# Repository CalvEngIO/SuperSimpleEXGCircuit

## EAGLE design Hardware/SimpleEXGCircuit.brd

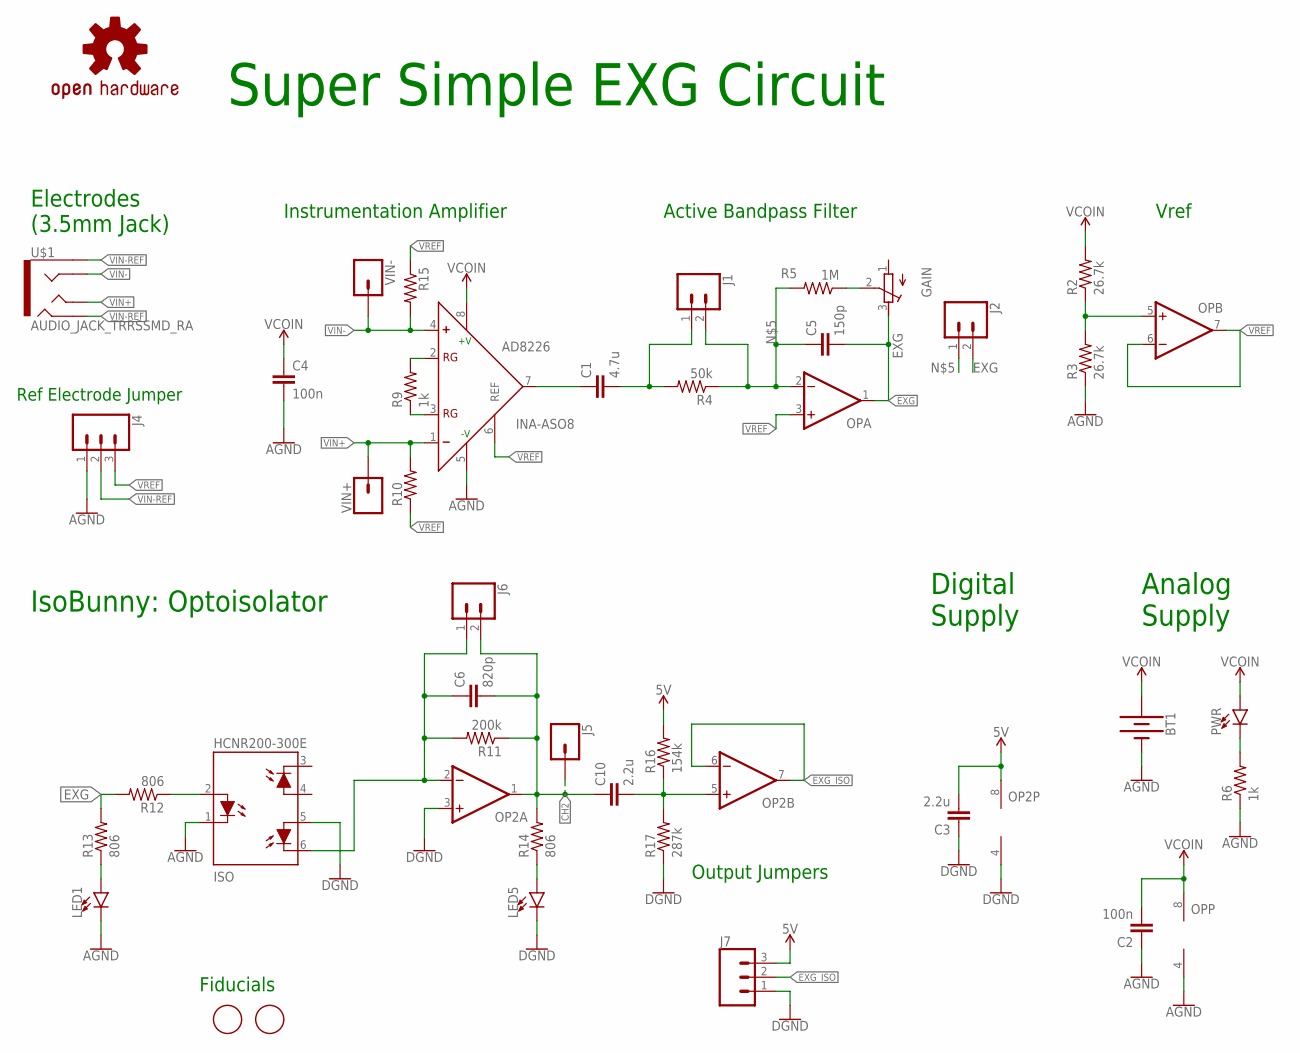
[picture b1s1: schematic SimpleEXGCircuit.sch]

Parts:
AD8226: INA-ASO8; SO8
BT1: BATTERY-20MM_SMD_4LEGS_OVERPASTE; BATTCON_20MM_4LEGS_OVERPASTE
C1: 4.7u; C0603
C2, C4: 100n; C0603
C3, C10: 2.2u; C0603
C5: 150p; C0603
C6: 820p; C0603
GAIN: TRIM-POT-P160; 16MMROTARYPOT
ISO: HCNR200-300E; DIP8-400
J1, J2, J6: CONN_02; 1X02
J4, J7: CONN_03; 1X03
J5: CONN_01PTH_NO_SILK_KIT; 1X01NS_KIT
LED1, LED5: LED1206; LED-1206
LOGO1: REVISION.C; REV.C
LOGO4: OSHW-LOGOL; OSHW-LOGO-L
OP, OP2: OP-DUALR; SO8
PWR: LED1206; LED-1206
R2, R3: 26.7k; R0603
R4: 50k; R0603
R5: 1M; R0603
R6, R9: 1k; R0603
R10, R15: RESISTOR0603; R0603
R11: 200k; R0603
R12, R13, R14: 806; R0603
R16: 154k; R0603
R17: 287k; R0603
U$1: AUDIO_JACK_TRRSSMD_RA; AUDIO_JACK_3.5MM_TRRS_SMD_RA
U$4: CALVENGIO_HANDLEHANDLE.05; CALVENGIO_HANDLE.05
U$5, U$6: FIDUCIAL; FIDUCIAL_1MM
VIN+: CONN_01; 1X01
VIN-: CONN_01; 1X01

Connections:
5V: C3.2, J7.3, OP2.8 (V+), R16.2
AGND: AD8226.5 (-V), BT1.2 (-), C2.1, C4.2, ISO.1 (C), J4.1, LED1.C, OP.4 (V-), R3.1, R6.1
CH2: C6.2, C10.1, J5.1, J6.2, OP2.1 (OUT), R11.1, R14.2
DGND: C3.1, ISO.5 (A2), J7.1, LED5.C, OP2.3 (+IN), OP2.4 (V-), R17.1
EXG: C5.2, GAIN.3 (E), J2.2, OP.1 (OUT), R12.2, R13.2
EXG_ISO: J7.2, OP2.6 (-IN), OP2.7 (OUT)
INA: AD8226.7 (OUT), C1.1
unnamed: GAIN.2 (S), R5.1
unnamed: AD8226.2 (RG), R9.2
unnamed: OP.5 (+IN), R2.1, R3.2
unnamed: C5.1, J1.2, J2.1, OP.2 (-IN), R4.1, R5.2
unnamed: PWR.C, R6.2
unnamed: AD8226.3 (RG), R9.1
unnamed: C1.2, J1.1, R4.2
unnamed: C6.1, ISO.6 (C2), J6.1, OP2.2 (-IN), R11.2
unnamed: ISO.2 (A), R12.1
unnamed: C10.2, OP2.5 (+IN), R16.1, R17.2
unnamed: LED1.A, R13.1
unnamed: LED5.A, R14.1
VCOIN: AD8226.8 (+V), BT1.1 (+), C2.2, C4.1, OP.8 (V+), PWR.A, R2.2
VIN+: AD8226.1 (IN-), R10.2, U$1.TIP, VIN+.1
VIN-: AD8226.4 (IN+), R15.2, U$1.RING1, VIN-.1
VIN-REF: J4.2, U$1.EARTH, U$1.RING2
VREF: AD8226.6 (REF), J4.3, OP.3 (+IN), OP.6 (-IN), OP.7 (OUT), R10.1, R15.1

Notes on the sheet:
Instrumentation Amplifier
Active Bandpass Filter
Vref
IsoBunny: Optoisolator
Electrodes (3.5mm Jack)
Ref Electrode Jumper
Analog Supply
Digital Supply
Output Jumpers
Super Simple EXG Circuit
Fiducials

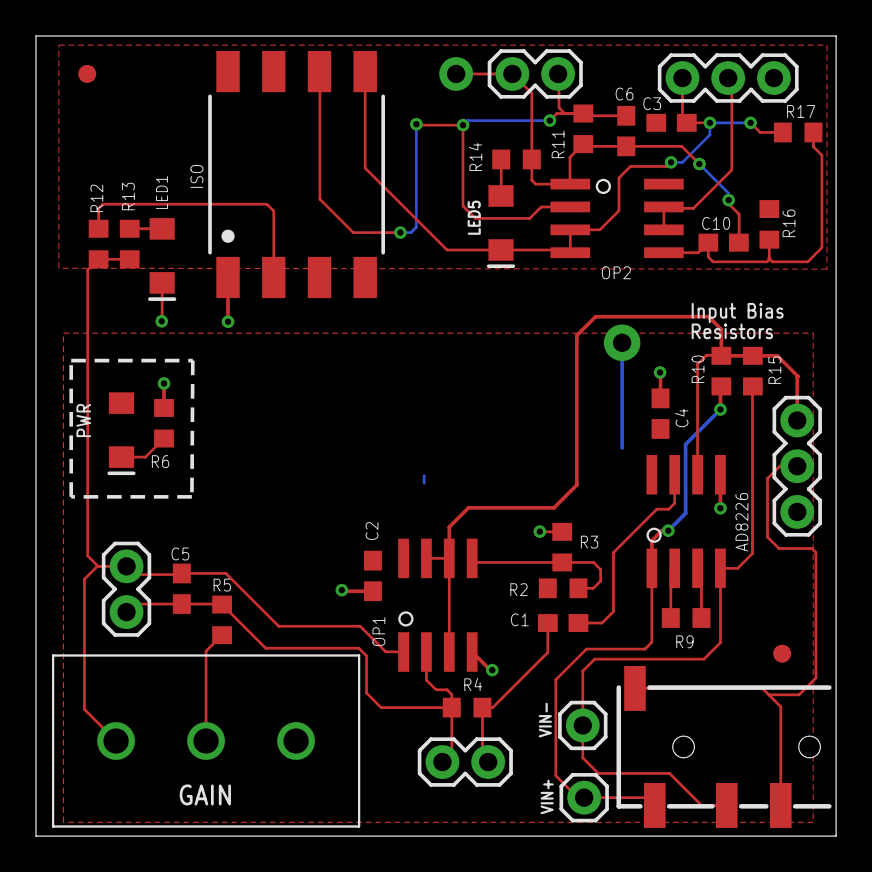
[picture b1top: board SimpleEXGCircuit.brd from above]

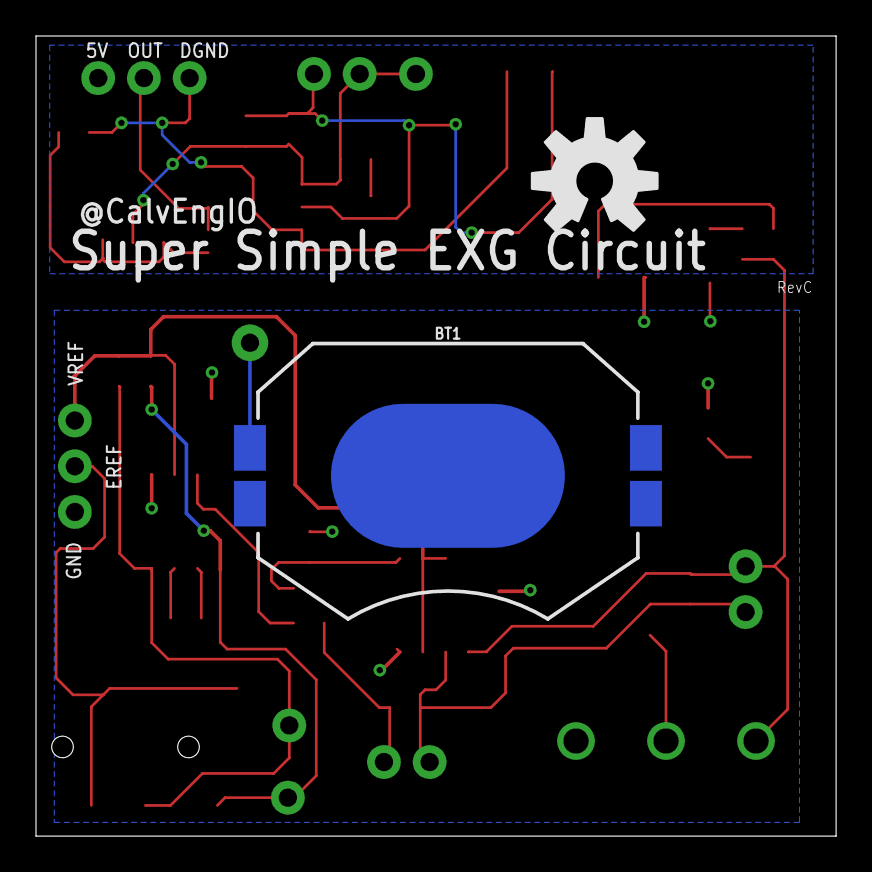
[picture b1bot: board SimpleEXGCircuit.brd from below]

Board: 2 copper layers, 44.5 x 44.5 mm, 44 parts (4 on the bottom side), 24 nets.

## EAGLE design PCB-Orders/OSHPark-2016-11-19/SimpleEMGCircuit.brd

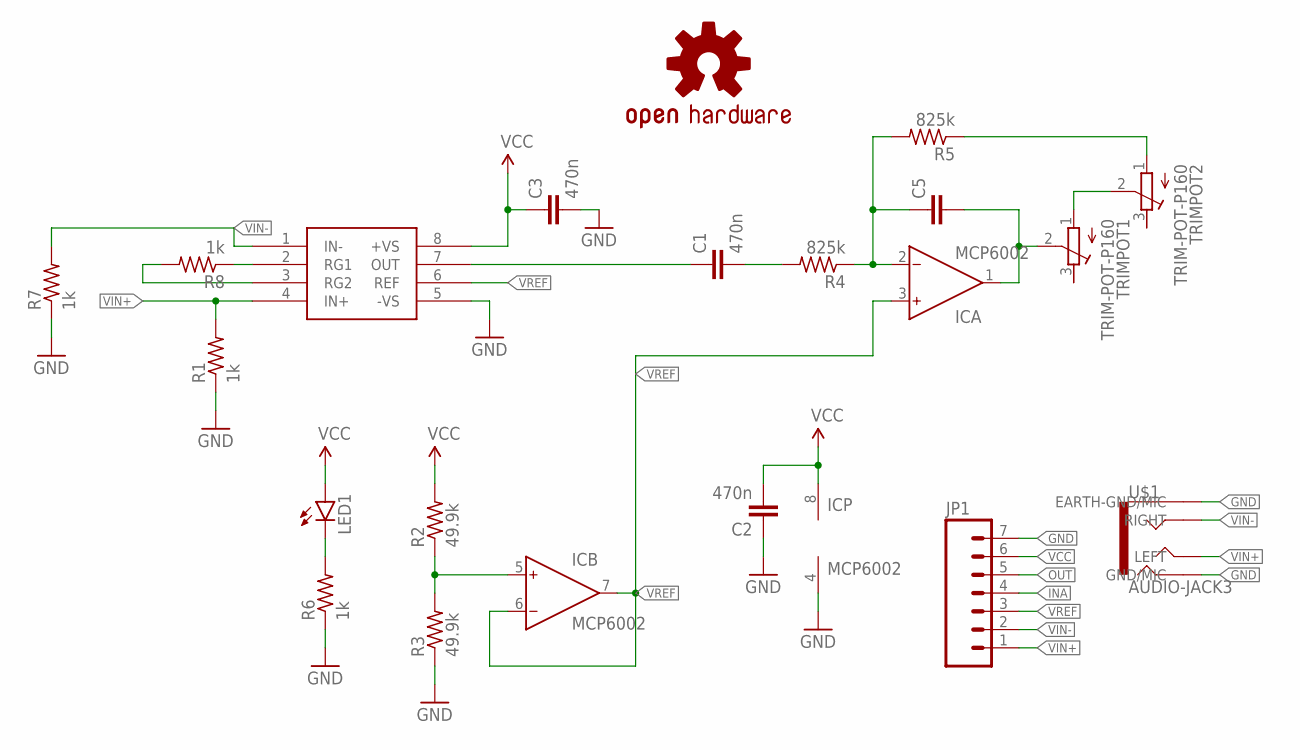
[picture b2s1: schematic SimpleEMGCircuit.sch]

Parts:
C1, C2, C3: 470n; C0402
C5: C-EU025-024X044; C025-024X044
IC: MCP6002; MSOP08
INA: AD8220; MSOP08
JP1: M07; 1X07
LED1: LED0603; LED-0603
LOGO1: OSHW-LOGOS; OSHW-LOGO-S
R1, R6, R7, R8: 1k; R0402
R2, R3: 49.9k; R0402
R4, R5: 825k; R0402
TRIMPOT1, TRIMPOT2: TRIM-POT-P160; 16MMROTARYPOT
U$1: AUDIO-JACK3; AUDIO-JACK-TRRS-SMD

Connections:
GND: C2.1, C3.2, IC.4 (V-), INA.5 (-VS), JP1.7, R1.1, R3.1, R6.1, R7.1, U$1.EARTH (EARTH-GND/MIC), U$1.RING2 (GND/MIC)
INA: C1.1, INA.7 (OUT), JP1.4
unnamed: TRIMPOT1.1 (A), TRIMPOT2.2 (S)
unnamed: R5.1, TRIMPOT2.1 (A)
unnamed: IC.5 (IN+), R2.1, R3.2
unnamed: C1.2, R4.2
unnamed: C5.1, IC.2 (IN-), R4.1, R5.2
unnamed: LED1.C, R6.2
unnamed: INA.2 (RG1), R8.1
unnamed: INA.3 (RG2), R8.2
OUT: C5.2, IC.1 (OUT), JP1.5, TRIMPOT1.2 (S)
VCC: C2.2, C3.1, IC.8 (V+), INA.8 (+VS), JP1.6, LED1.A, R2.2
VIN+: INA.4 (IN+), JP1.1, R1.2, U$1.TIP (LEFT)
VIN-: INA.1 (IN-), JP1.2, R7.2, U$1.RING1 (RIGHT)
VREF: IC.3 (IN+), IC.6 (IN-), IC.7 (OUT), INA.6 (REF), JP1.3

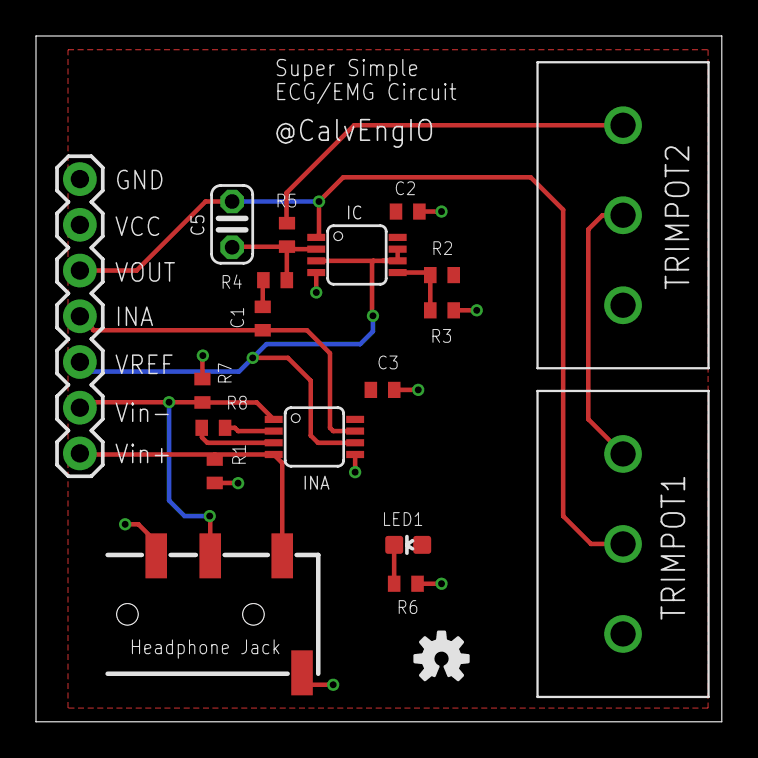
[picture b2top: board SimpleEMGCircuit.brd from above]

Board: 2 copper layers, 38.1 x 38.1 mm, 20 parts (0 on the bottom side), 15 nets.

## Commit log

2017-05-08 added older PCB orders
2019-04-14 new hardware design with optoisolator and coin cell battery

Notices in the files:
PCB-Orders/OSHPark-2016-11-19/SimpleEMGCircuit.brd:
Creative Commons License
CC BY-SA-4.0
parts and their libraries:
SparkFun-Connectors: Licensing: Creative Commons ShareAlike 4.0 International - https://creativecommons.org/licenses/by-sa/4.0
